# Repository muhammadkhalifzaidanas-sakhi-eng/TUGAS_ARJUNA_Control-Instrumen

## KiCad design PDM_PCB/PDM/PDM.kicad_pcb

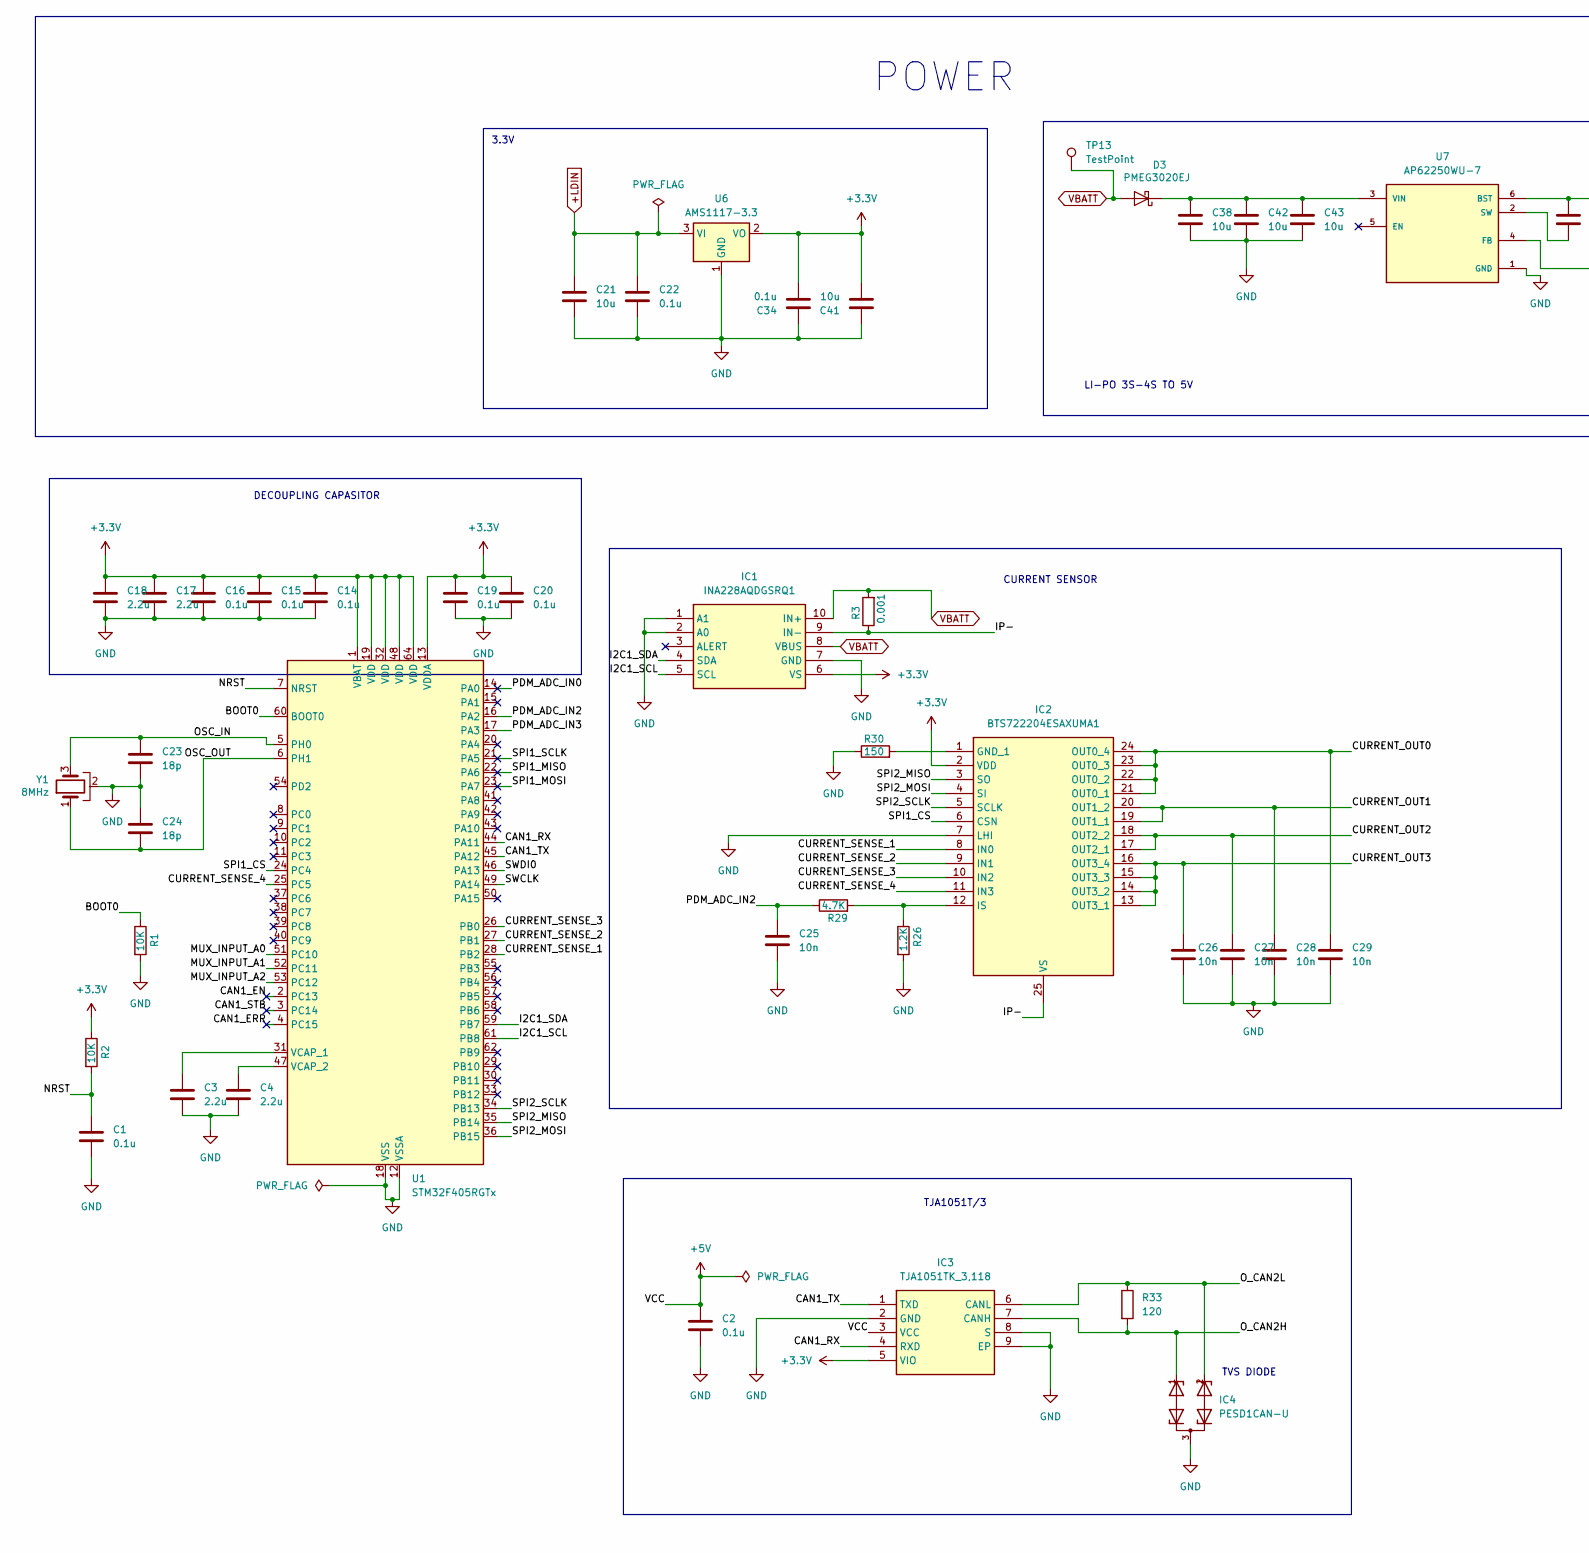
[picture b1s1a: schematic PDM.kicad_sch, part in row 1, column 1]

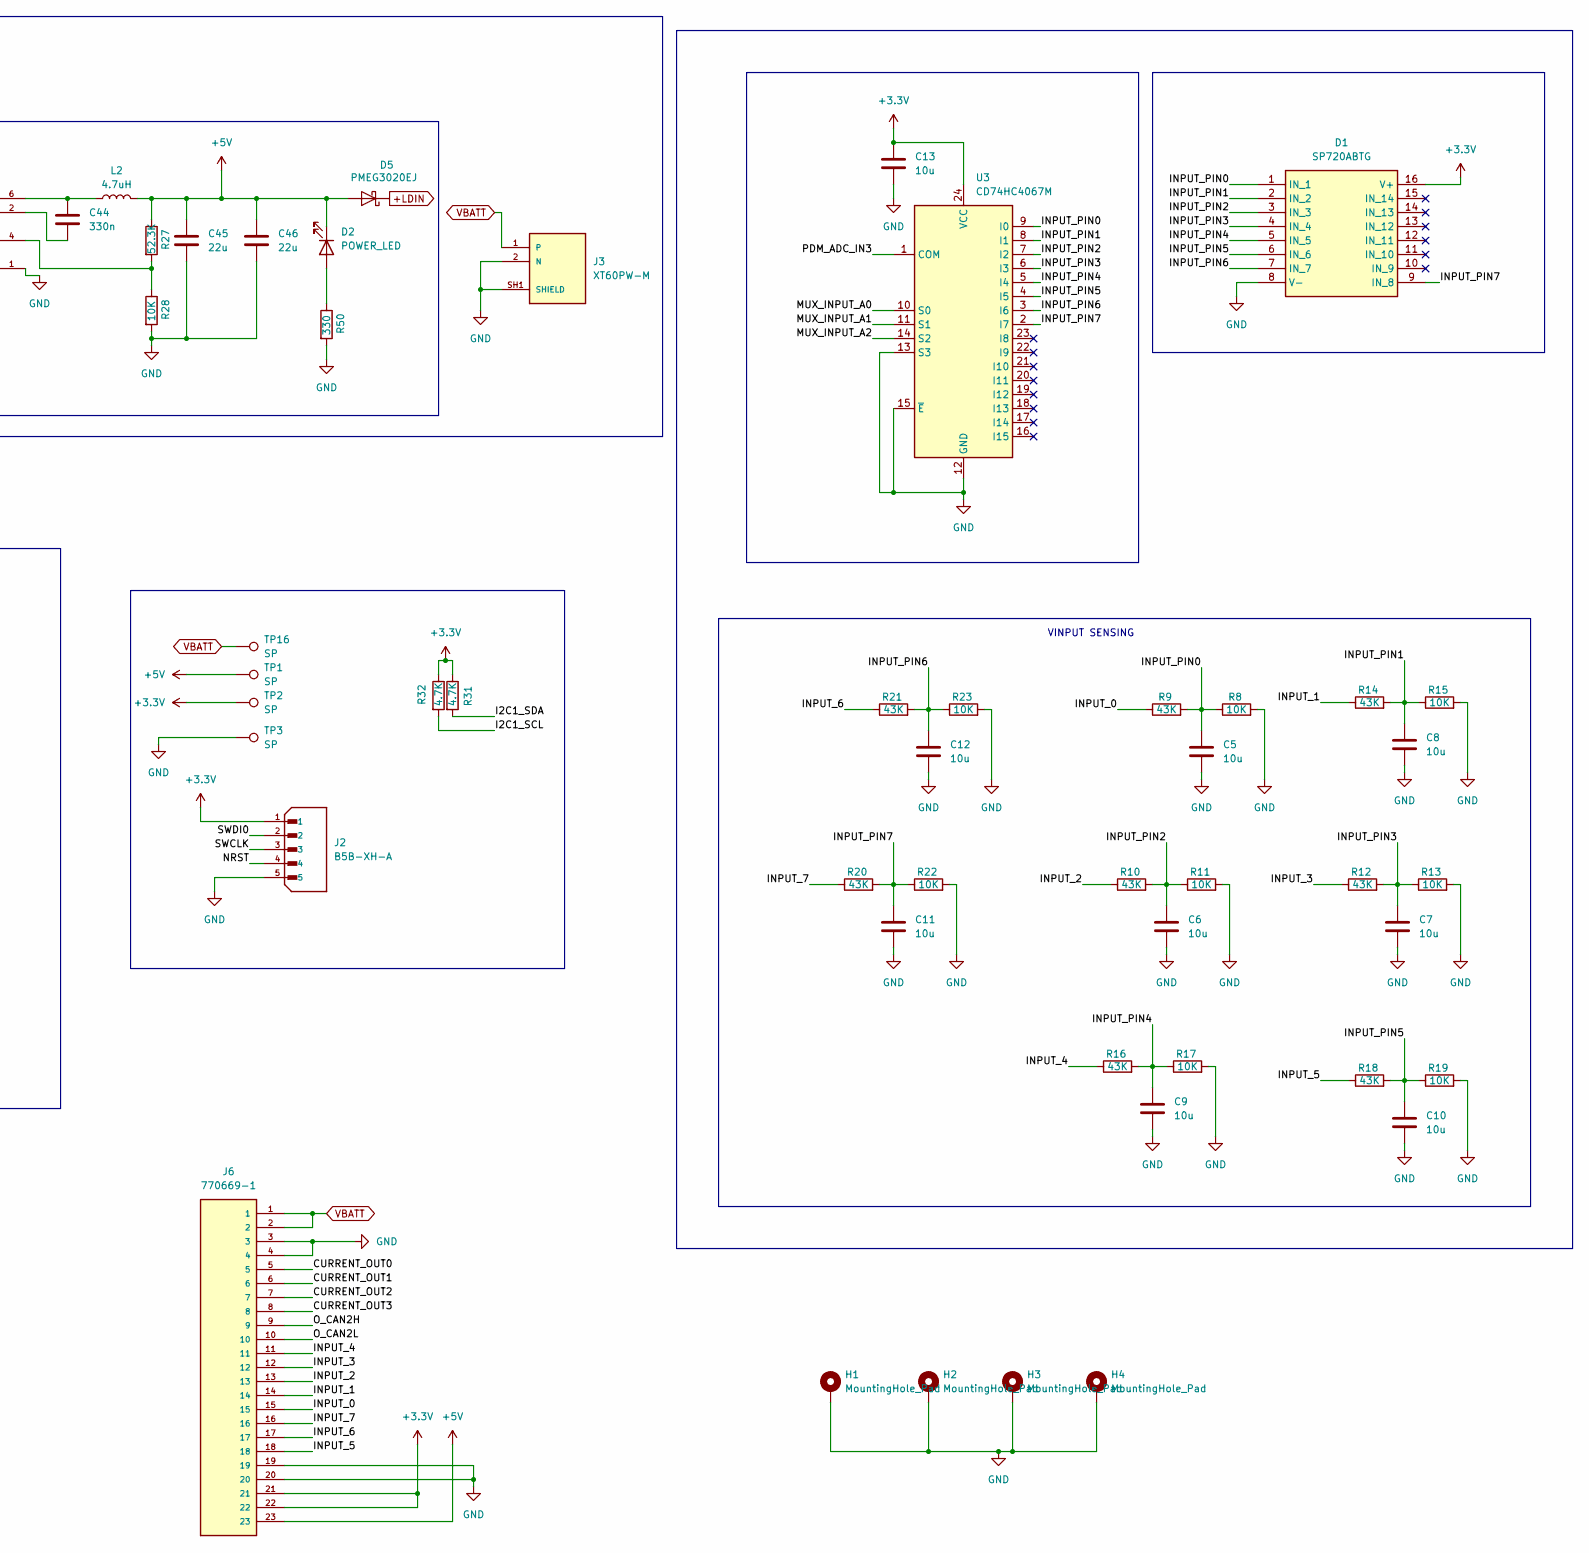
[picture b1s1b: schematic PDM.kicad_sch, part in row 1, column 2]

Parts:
C1, C2, C14, C15, C16, C19, C20, C22, C34: 0.1u; C_0603_1608Metric
C3, C4, C17, C18: 2.2u; C_0603_1608Metric
C5, C6, C7, C8, C9, C10, C11, C12, C13, C21, C38, C41, C42, C43: 10u; C_0805_2012Metric
C23, C24: 18p; C_0603_1608Metric
C25, C26, C27, C28, C29: 10n; C_0805_2012Metric
C44: 330n; C_0603_1608Metric
C45, C46: 22u; C_0805_2012Metric
D1: SP720ABTG; SOIC-16_3.9x9.9mm_P1.27mm; Manufacturer_Part_Number SP720ABTG; Mouser Part Number 576-SP720ABTG
D2: POWER_LED; LED_0603_1608Metric
D3, D5: PMEG3020EJ; D_SOD-323F
H1, H2, H3, H4: MountingHole_Pad; MountingHole_3.2mm_M3_Pad
IC1: INA228AQDGSRQ1; SOP50P490X110-10N; Manufacturer_Part_Number INA228AQDGSRQ1; Mouser Part Number 595-INA228AQDGSRQ1
IC2: BTS722204ESAXUMA1; SOP65P600X115-25N; Manufacturer_Part_Number BTS722204ESAXUMA1; Mouser Part Number 726-BTS722204ESAXUMA
IC3: TJA1051TK_3,118; SON65P300X300X100-9N-D; Manufacturer_Part_Number TJA1051TK/3,118; Mouser Part Number 771-TJA1051TK/3118
IC4: PESD1CAN-U; PG-SOT23
J2: B5B-XH-A; JST_B5B-XH-A; PARTREV 7/4/21
J3: XT60PW-M; AMASS_XT60PW-M; PARTREV 1.2
J6: 770669-1; TE_770669-1; PARTREV K11
L2: 4.7uH; L_Taiyo-Yuden_NR-30xx_HandSoldering
R1, R2, R8, R11, R13, R15, R17, R19, R22, R23, R28: 10K; R_0603_1608Metric
R3: 0.001; R_0603_1608Metric
R9, R10, R12, R14, R16, R18, R20, R21: 43K; R_0603_1608Metric
R26: 1.2K; R_0603_1608Metric
R27: 52.3K; R_0603_1608Metric
R29, R31, R32: 4.7K; R_0603_1608Metric
R30: 150; R_0603_1608Metric
R33: 120; R_0603_1608Metric
R50: 330; R_0603_1608Metric
TP1, TP2, TP3, TP16: SP; TestPoint_THTPad_2.0x2.0mm_Drill1.0mm
TP13: TestPoint; TestPoint_THTPad_2.0x2.0mm_Drill1.0mm
U1: STM32F405RGTx; LQFP-64_10x10mm_P0.5mm
U3: CD74HC4067M; SOIC-24W_7.5x15.4mm_P1.27mm
U6: AMS1117-3.3; SOT-223-3_TabPin2
U7: AP62250WU-7; SOT95P280X100-6N; PARTREV Rev. 2-2
Y1: 8MHz; Crystal_SMD_3225-4Pin_3.2x2.5mm

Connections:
+3.3V: C13.1, C14.1, C15.1, C16.1, C17.1, C18.1, C19.1, C20.1, C34.2, C41.2, D1.16 (V+), IC1.6 (VS), IC2.2 (VDD), IC3.5 (VIO), J2.1, J6.21, J6.22, R2.1, R31.1, R32.1, TP2.1, U1.1 (VBAT), U1.13 (VDDA), U1.19 (VDD), U1.32 (VDD), U1.48 (VDD), U1.64 (VDD), U3.24 (VCC), U6.2 (VO); also elsewhere on the board
+5V: C2.1, C45.1, C46.1, D2.1 (K), D5.2 (A), IC3.3 (VCC), J6.23, L2.2, R27.1, TP1.1; also elsewhere on the board
+LDIN: C21.1, C22.1, D5.1 (K), U6.3 (VI)
/BOOT0: R1.1, U1.60 (BOOT0)
/CAN1_EN: U1.2 (PC13)
/CAN1_ERR: U1.4 (PC15)
/CAN1_RX: IC3.4 (RXD), U1.44 (PA11)
/CAN1_STB: U1.3 (PC14)
/CAN1_TX: IC3.1 (TXD), U1.45 (PA12)
/CURRENT_OUT0: C29.1, IC2.21 (OUT0_1), IC2.22 (OUT0_2), IC2.23 (OUT0_3), IC2.24 (OUT0_4), J6.5
/CURRENT_OUT1: C28.1, IC2.19 (OUT1_1), IC2.20 (OUT1_2), J6.6
/CURRENT_OUT2: C27.1, IC2.17 (OUT2_1), IC2.18 (OUT2_2), J6.7
/CURRENT_OUT3: C26.1, IC2.13 (OUT3_1), IC2.14 (OUT3_2), IC2.15 (OUT3_3), IC2.16 (OUT3_4), J6.8
/CURRENT_SENSE_1: IC2.8 (IN0), U1.28 (PB2)
/CURRENT_SENSE_2: IC2.9 (IN1), U1.27 (PB1)
/CURRENT_SENSE_3: IC2.10 (IN2), U1.26 (PB0)
/CURRENT_SENSE_4: IC2.11 (IN3), U1.25 (PC5)
/I2C1_SCL: IC1.5 (SCL), R32.2, U1.61 (PB8)
/I2C1_SDA: IC1.4 (SDA), R31.2, U1.59 (PB7)
/INPUT_0: J6.15, R9.1
/INPUT_1: J6.14, R14.1
/INPUT_2: J6.13, R10.1
/INPUT_3: J6.12, R12.1
/INPUT_4: J6.11, R16.1
/INPUT_5: J6.18, R18.1
/INPUT_6: J6.17, R21.1
/INPUT_7: J6.16, R20.1
/INPUT_PIN0: C5.1, D1.1 (IN_1), R8.1, R9.2, U3.9 (I0)
/INPUT_PIN1: C8.1, D1.2 (IN_2), R14.2, R15.1, U3.8 (I1)
/INPUT_PIN2: C6.1, D1.3 (IN_3), R10.2, R11.1, U3.7 (I2)
/INPUT_PIN3: C7.1, D1.4 (IN_4), R12.2, R13.1, U3.6 (I3)
/INPUT_PIN4: C9.1, D1.5 (IN_5), R16.2, R17.1, U3.5 (I4)
/INPUT_PIN5: C10.1, D1.6 (IN_6), R18.2, R19.1, U3.4 (I5)
/INPUT_PIN6: C12.1, D1.7 (IN_7), R21.2, R23.1, U3.3 (I6)
/INPUT_PIN7: C11.1, D1.9 (IN_8), R20.2, R22.1, U3.2 (I7)
/IP-: IC1.9 (IN-), IC2.25 (VS), R3.1
/MUX_INPUT_A0: U1.51 (PC10), U3.10 (S0)
/MUX_INPUT_A1: U1.52 (PC11), U3.11 (S1)
/MUX_INPUT_A2: U1.53 (PC12), U3.14 (S2)
/NRST: C1.1, J2.4, R2.2, U1.7 (NRST)
/OSC_IN: C23.1, U1.5 (PH0), Y1.3
/OSC_OUT: C24.2, U1.6 (PH1), Y1.1
/O_CAN2H: IC3.7 (CANH), IC4.1, J6.9, R33.2
/O_CAN2L: IC3.6 (CANL), IC4.2, J6.10, R33.1
/PDM_ADC_IN0: U1.14 (PA0)
/PDM_ADC_IN2: C25.1, R29.1, U1.16 (PA2)
/PDM_ADC_IN3: U1.17 (PA3), U3.1 (COM)
/SPI1_CS: IC2.6 (CSN), U1.24 (PC4)
/SPI1_MISO: U1.22 (PA6)
/SPI1_MOSI: U1.23 (PA7)
/SPI1_SCLK: U1.21 (PA5)
/SPI2_MISO: IC2.3 (SO), U1.35 (PB14)
/SPI2_MOSI: IC2.4 (SI), U1.36 (PB15)
/SPI2_SCLK: IC2.5 (SCLK), U1.34 (PB13)
/SWCLK: J2.3, U1.49 (PA14)
/SWDI0: J2.2, U1.46 (PA13)
GND: C1.2, C2.2, C3.2, C4.2, C5.2, C6.2, C7.2, C8.2, C9.2, C10.2, C11.2, C12.2, C13.2, C14.2, C15.2, C16.2, C17.2, C18.2, C19.2, C20.2, C21.2, C22.2, C23.2, C24.1, C25.2, C26.2, C27.2, C28.2, C29.2, C34.1, C38.2, C41.1, C42.2, C43.2, C45.2, C46.2, D1.8 (V-), H1.1, H2.1, H3.1, H4.1, IC1.1 (A1), IC1.2 (A0), IC1.7 (GND), IC2.7 (LHI), IC3.2 (GND), IC3.8 (S), IC3.9 (EP), IC4.3, J2.5, J3.2 (N), J3.SH1 (SHIELD), J3.SH2 (SHIELD), J6.3, J6.4, J6.19, J6.20, R1.2, R8.2, R11.2, R13.2, R15.2, R17.2, R19.2, R22.2, R23.2, R26.2, R28.2, R30.1, R50.2, TP3.1, U1.12 (VSSA), U1.18 (VSS), U1.63 (VSS), U3.12 (GND), U3.13 (S3), U3.15 (~E), U6.1 (GND), U7.1 (GND), Y1.2, Y1.4; also elsewhere on the board
unnamed: D2.2 (A), R50.1
unnamed: C38.1, C42.1, C43.1, D3.1 (K), U7.3 (VIN)
unnamed: IC2.1 (GND_1), R30.2
unnamed: IC2.12 (IS), R26.1, R29.2
unnamed: C3.1, U1.31 (VCAP_1)
unnamed: C4.1, U1.47 (VCAP_2)
unnamed: C44.1, L2.1, U7.6 (BST)
unnamed: R27.2, R28.1, U7.4 (FB)
unnamed: C44.2, U7.2 (SW)
VBATT: D3.2 (A), IC1.8 (VBUS), IC1.10 (IN+), J3.1, J6.1, J6.2, R3.2, TP13.1, TP16.1; also elsewhere on the board

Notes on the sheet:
CURRENT SENSOR
TVS DIODE
3.3V
VINPUT SENSING
TJA1051T/3
DECOUPLING CAPASITOR
POWER
LI-PO 3S-4S TO 5V

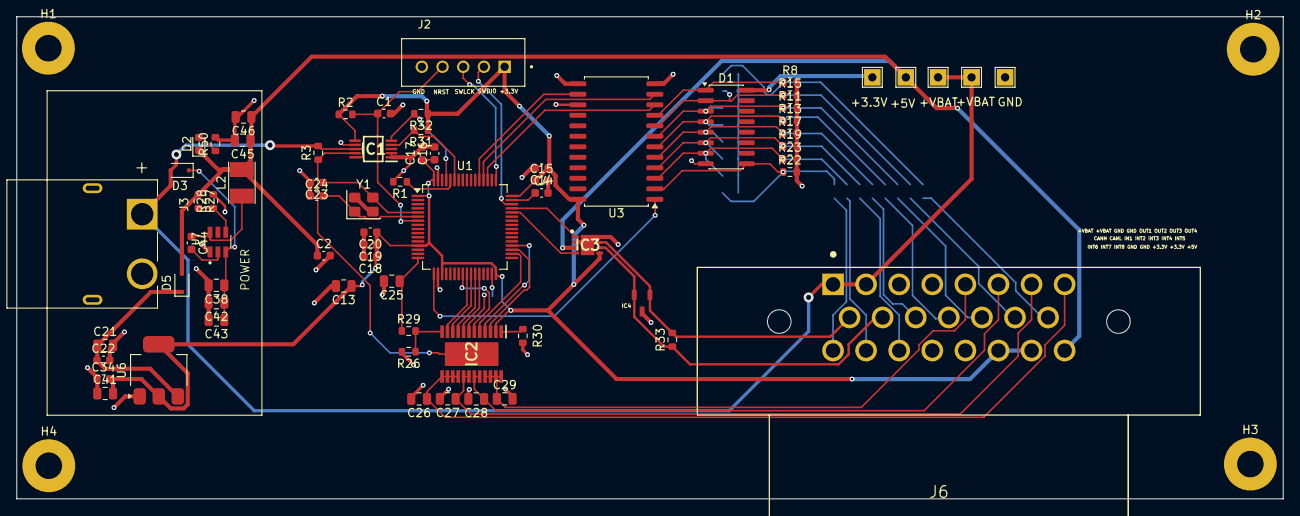
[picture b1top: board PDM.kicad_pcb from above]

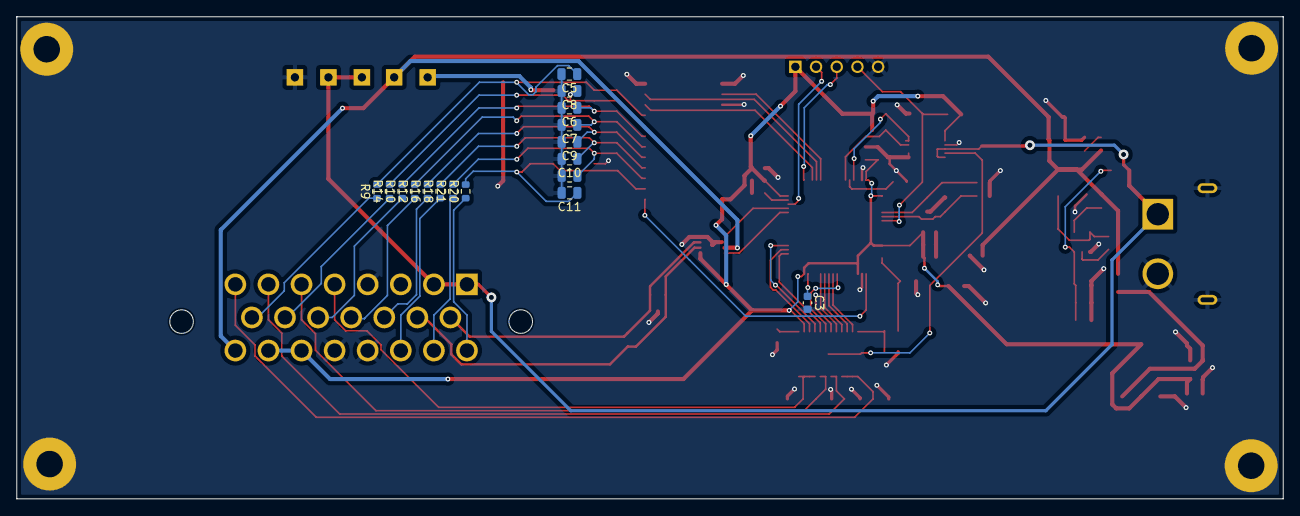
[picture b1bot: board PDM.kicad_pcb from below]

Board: 2 copper layers, 153.1 x 58.3 mm, 91 parts (17 on the bottom side), 60 nets.

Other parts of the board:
+3.3V, +5V: SP; TestPoint_THTPad_2.0x2.0mm_Drill1.0mm
+VBAT: SP; TestPoint_THTPad_2.0x2.0mm_Drill1.0mm
+VBAT#2: TestPoint; TestPoint_THTPad_2.0x2.0mm_Drill1.0mm
GND: SP; TestPoint_THTPad_2.0x2.0mm_Drill1.0mm

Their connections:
+3.3V: +3.3V.1; also elsewhere on the board
+5V: +5V.1; also elsewhere on the board
GND: GND.1; also elsewhere on the board
VBATT: +VBAT.1, +VBAT#2.1; also elsewhere on the board
